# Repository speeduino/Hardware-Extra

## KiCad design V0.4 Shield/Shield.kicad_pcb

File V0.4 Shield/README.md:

<div align="center">

[]

##### A low cost, DIY friendly Engine Management System (ECU) based on the Arduino framework
</div>

## Speeduino
The Speeduino project is a flexible, fully featured Engine Management Systems (EMS aka ECU) based on the low cost and open source Arduino platform. It provides the hardware, firmware and software components that make up an engine management system, all provided under open licenses. With over 1000 installations, Speeduino has matured into a product that meets the needs of the hobbyist and enthusiast community without driving prices to the levels of traditional aftermarket ECUs.

## Overview
This board is a shield designed to add an automotive connector to the v0.4 series of Speeduino ECUs. It also includes a VR conditioner on board and allows for 12v Hall effect signals (Such as on some GM engines) to be used directly. 

The connector used is a Delphi Sicma 39 pin 

## License
These designs are release under the [TAPR Open Hardware License v1.0](https://files.tapr.org/OHL/TAPR_Open_Hardware_License_v1.0.txt). 

## Support
In addition the manual referenced above, Speeduino has a large and very vibrant community of people to help out with your setup or any questions you might add. 

* [Speeduino Forum](https://speeduino.com/forum) 
* [Discord](hhttps://discord.com/invite/taXeNM6xNb)
* [Facebook](https://www.facebook.com/groups/191918764521976/)

## Contributors

This project exists thanks to all the people who contribute, both in terms of code and testing provided. If you'd like to get involved, please have a read through [Contributing](contributing.md) and then jump on Discord to discuss things further

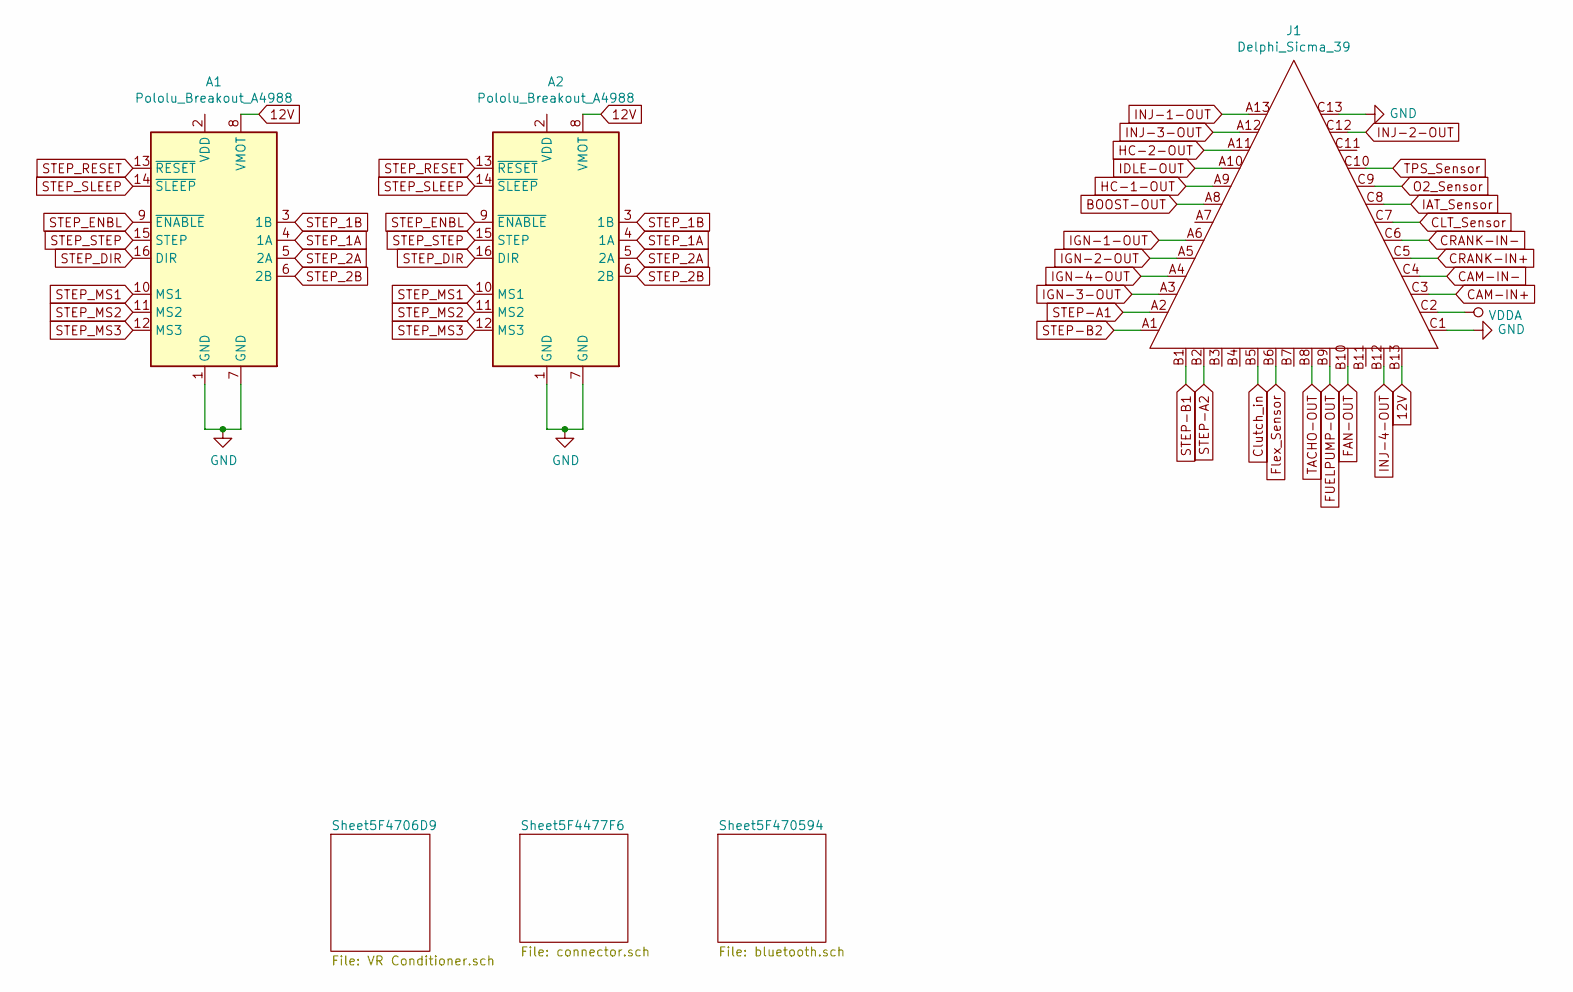
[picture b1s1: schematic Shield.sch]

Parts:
A1, A2: Pololu_Breakout_A4988; Pololu_Breakout-16_15.2x20.3mm; Manufacturer_Part_Number ESQ-108-14-L-S; Digikey Part Number SAM15571-ND
J1: Delphi_Sicma_39; Delphi_Sicma_39_Black

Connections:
12V: A1.8 (VMOT), A2.8 (VMOT), J1.B13
BOOST-OUT: J1.A8; also elsewhere on the board
CAM-IN+: J1.C3; also elsewhere on the board
CAM-IN-: J1.C4; also elsewhere on the board
CLT_Sensor: J1.C7; also elsewhere on the board
CRANK-IN+: J1.C5; also elsewhere on the board
CRANK-IN-: J1.C6; also elsewhere on the board
Clutch_in: J1.B5; also elsewhere on the board
FAN-OUT: J1.B10; also elsewhere on the board
FUELPUMP-OUT: J1.B9; also elsewhere on the board
Flex_Sensor: J1.B6; also elsewhere on the board
GND: A1.1 (GND), A1.7 (GND), A2.1 (GND), A2.7 (GND), J1.C1, J1.C13; also elsewhere on the board
HC-1-OUT: J1.A9; also elsewhere on the board
HC-2-OUT: J1.A11; also elsewhere on the board
IAT_Sensor: J1.C8; also elsewhere on the board
IDLE-OUT: J1.A10; also elsewhere on the board
IGN-1-OUT: J1.A6; also elsewhere on the board
IGN-2-OUT: J1.A5; also elsewhere on the board
IGN-3-OUT: J1.A3; also elsewhere on the board
IGN-4-OUT: J1.A4; also elsewhere on the board
INJ-1-OUT: J1.A13; also elsewhere on the board
INJ-2-OUT: J1.C12; also elsewhere on the board
INJ-3-OUT: J1.A12; also elsewhere on the board
INJ-4-OUT: J1.B12; also elsewhere on the board
O2_Sensor: J1.C9; also elsewhere on the board
STEP-A1: J1.A2; also elsewhere on the board
STEP-A2: J1.B2; also elsewhere on the board
STEP-B1: J1.B1; also elsewhere on the board
STEP-B2: J1.A1; also elsewhere on the board
STEP_1A: A1.4 (1A), A2.4 (1A)
STEP_1B: A1.3 (1B), A2.3 (1B)
STEP_2A: A1.5 (2A), A2.5 (2A)
STEP_2B: A1.6 (2B), A2.6 (2B)
STEP_DIR: A1.16 (DIR), A2.16 (DIR)
STEP_ENBL: A1.9 (~ENABLE), A2.9 (~ENABLE)
STEP_MS1: A1.10 (MS1), A2.10 (MS1)
STEP_MS2: A1.11 (MS2), A2.11 (MS2)
STEP_MS3: A1.12 (MS3), A2.12 (MS3)
STEP_RESET: A1.13 (~RESET), A2.13 (~RESET)
STEP_SLEEP: A1.14 (~SLEEP), A2.14 (~SLEEP)
STEP_STEP: A1.15 (STEP), A2.15 (STEP)
TACHO-OUT: J1.B8; also elsewhere on the board
TPS_Sensor: J1.C10; also elsewhere on the board
VDDA: J1.C2; also elsewhere on the board

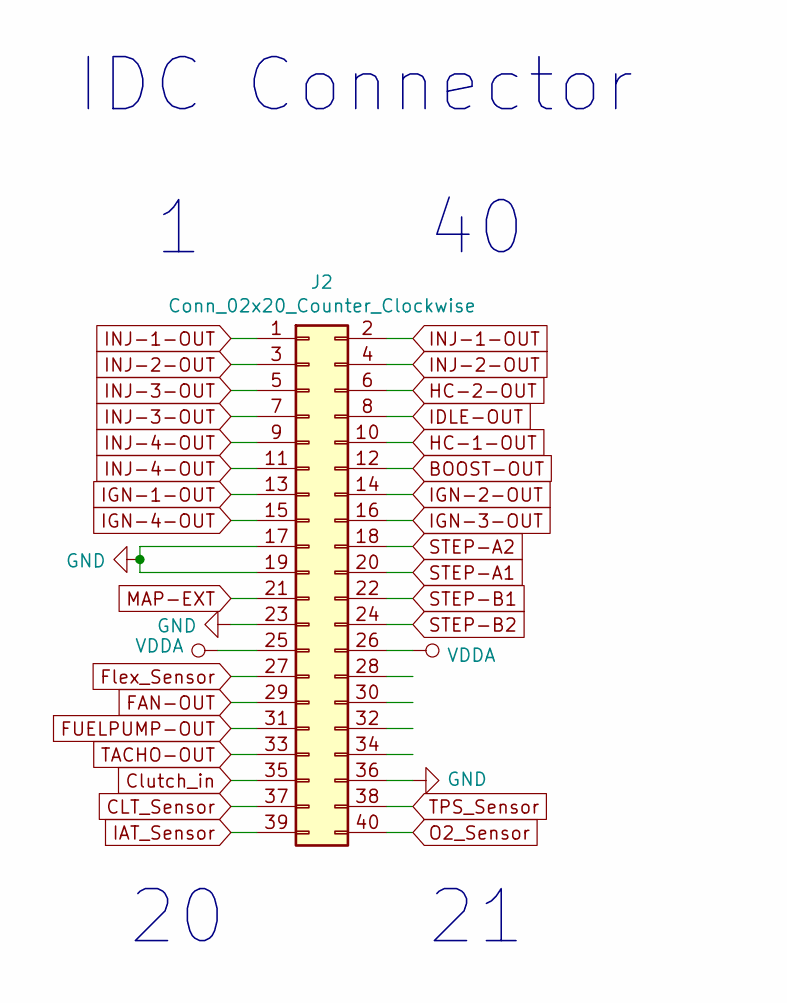
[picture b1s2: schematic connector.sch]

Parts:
J2: Conn_02x20_Counter_Clockwise; IDC-Header_2x20_P2.54mm_Vertical; Manufacturer_Part_Number SFH11-PBPC-D20-ST-BK; Digikey Part Number S9200-ND

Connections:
BOOST-OUT: J2.12; also elsewhere on the board
CLT_Sensor: J2.37; also elsewhere on the board
Clutch_in: J2.35; also elsewhere on the board
FAN-OUT: J2.29; also elsewhere on the board
FUELPUMP-OUT: J2.31; also elsewhere on the board
Flex_Sensor: J2.27; also elsewhere on the board
GND: J2.17, J2.19, J2.23, J2.36; also elsewhere on the board
HC-1-OUT: J2.10; also elsewhere on the board
HC-2-OUT: J2.6; also elsewhere on the board
IAT_Sensor: J2.39; also elsewhere on the board
IDLE-OUT: J2.8; also elsewhere on the board
IGN-1-OUT: J2.13; also elsewhere on the board
IGN-2-OUT: J2.14; also elsewhere on the board
IGN-3-OUT: J2.16; also elsewhere on the board
IGN-4-OUT: J2.15; also elsewhere on the board
INJ-1-OUT: J2.1, J2.2; also elsewhere on the board
INJ-2-OUT: J2.3, J2.4; also elsewhere on the board
INJ-3-OUT: J2.5, J2.7; also elsewhere on the board
INJ-4-OUT: J2.9, J2.11; also elsewhere on the board
MAP-EXT: J2.21
O2_Sensor: J2.40; also elsewhere on the board
STEP-A1: J2.20; also elsewhere on the board
STEP-A2: J2.18; also elsewhere on the board
STEP-B1: J2.22; also elsewhere on the board
STEP-B2: J2.24; also elsewhere on the board
TACHO-OUT: J2.33; also elsewhere on the board
TPS_Sensor: J2.38; also elsewhere on the board
VDDA: J2.25, J2.26; also elsewhere on the board

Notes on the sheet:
IDC Connector

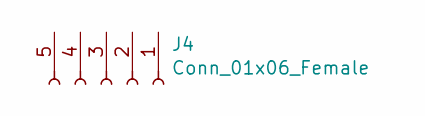
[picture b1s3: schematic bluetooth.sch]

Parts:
J4: Conn_01x06_Female; PinHeader_1x06_P2.54mm_Vertical

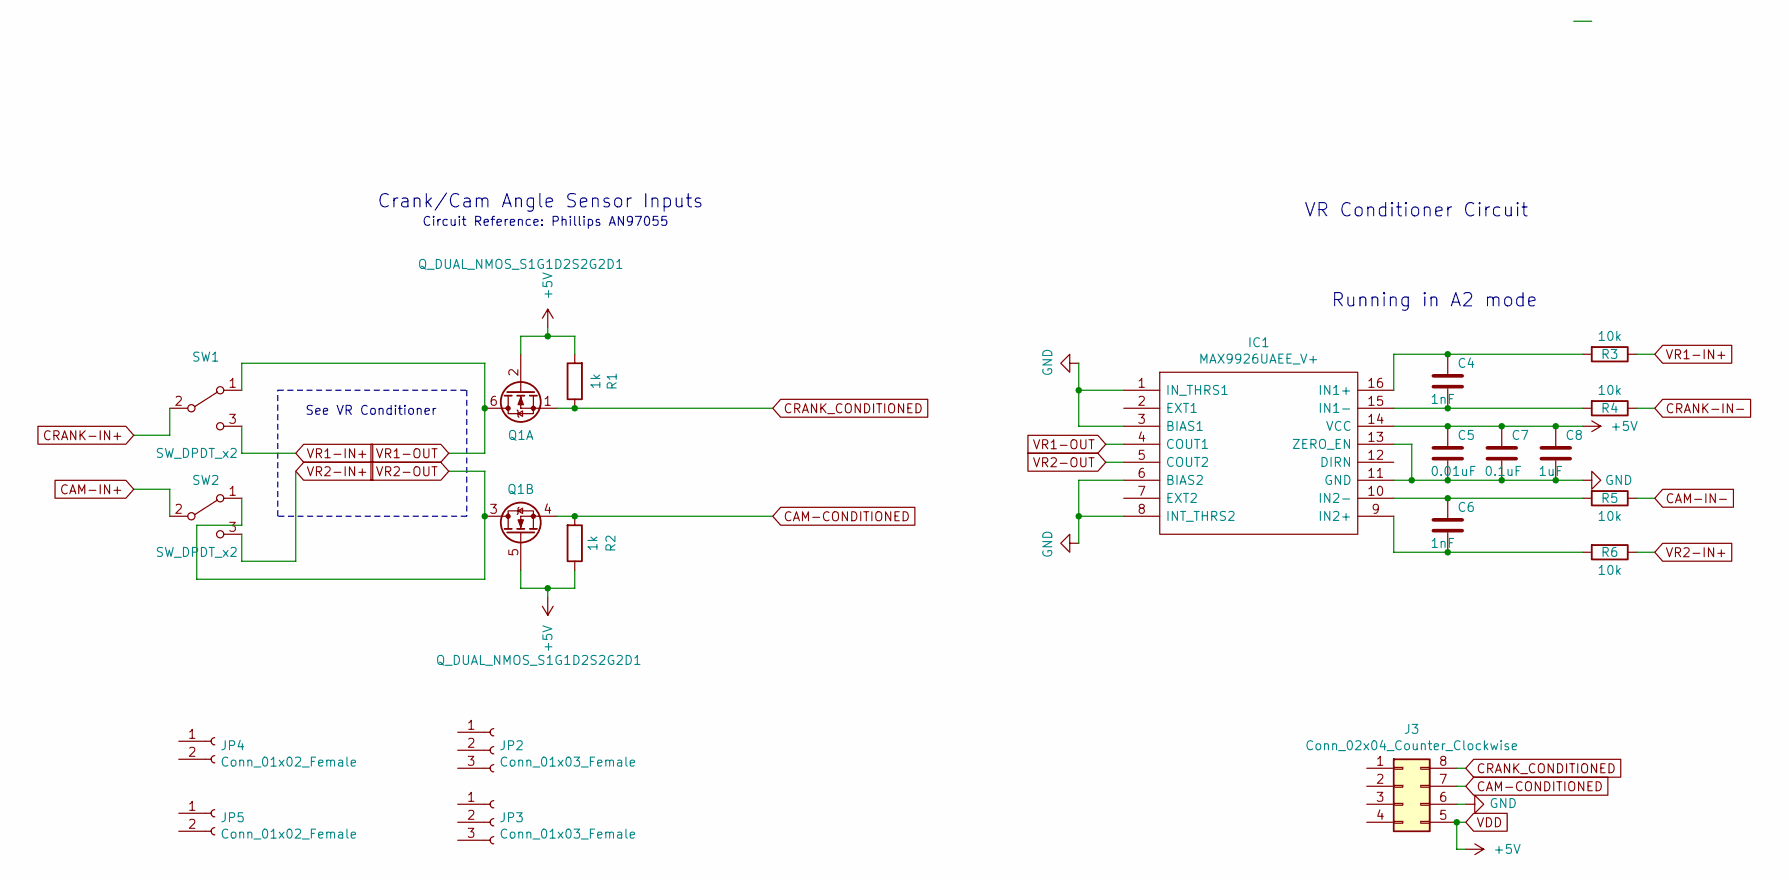
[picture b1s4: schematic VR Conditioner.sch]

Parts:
C4, C6: 1nF; C_0805_2012Metric; Manufacturer_Part_Number C0805C102J5HACAUTO; Digikey Part Number 399-16591-1-ND
C5: 0.01uF; C_0805_2012Metric; Manufacturer_Part_Number CC0805KRX7R9BB103; Digikey Part Number 311-1136-1-ND
C7: 0.1uF; C_0805_2012Metric; Manufacturer_Part_Number C0805C104M5RACAUTO; Digikey Part Number 399-12977-1-ND
C8: 1uF; C_0805_2012Metric; Manufacturer_Part_Number C0805C105K4RACAUTO; Digikey Part Number 399-6930-1-ND
IC1: MAX9926UAEE_V+; QSOP-16_3.9x4.9mm_P0.635mm; Manufacturer_Part_Number MAX9926UAEE/V+; Mouser Part Number 700-MAX9926UAEE/V+
J3: Conn_02x04_Counter_Clockwise; DIP-8_W7.62mm
JP2, JP3: Conn_01x03_Female; PinHeader_1x03_P2.54mm_Vertical
JP4, JP5: Conn_01x02_Female; PinHeader_1x02_P2.54mm_Vertical
Q1: Q_DUAL_NMOS_S1G1D2S2G2D1; SOT-363_SC-70-6; Manufacturer_Part_Number NTJD5121NT1G; Digikey Part Number NTJD5121NT1GOSCT-ND
R1, R2: 1k; R_0805_2012Metric; Manufacturer_Part_Number RC0805FR-071KL; Digikey Part Number 311-1.00KCRCT-ND
R3, R4, R5, R6: 10k; R_0805_2012Metric; Manufacturer_Part_Number RC0805JR-0710KL; Digikey Part Number 311-10KARCT-ND
SW1, SW2: SW_DPDT_x2; AYZ0202AGRLC; Manufacturer_Part_Number AYZ0202AGRLC; Digikey Part Number 401-2013-1-ND

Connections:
CAM-CONDITIONED: J3.7, Q1.4 (S), R2.2
CAM-IN+: SW2.2 (B); also elsewhere on the board
CAM-IN-: R5.1; also elsewhere on the board
CRANK-IN+: SW1.2 (B); also elsewhere on the board
CRANK-IN-: R4.1; also elsewhere on the board
CRANK_CONDITIONED: J3.8, Q1.1 (S), R1.1
GND: C5.2, C7.2, C8.2, IC1.1 (IN_THRS1), IC1.3 (BIAS1), IC1.6 (BIAS2), IC1.8 (INT_THRS2), IC1.11 (GND), IC1.13 (ZERO_EN), J3.6; also elsewhere on the board
unnamed: C4.1, IC1.16 (IN1+), R3.2
unnamed: C4.2, IC1.15 (IN1-), R4.2
unnamed: C6.1, IC1.10 (IN2-), R5.2
unnamed: C6.2, IC1.9 (IN2+), R6.2
VDD: C5.1, C7.1, C8.1, IC1.14 (VCC), J3.5, Q1.2 (G), Q1.5 (G), R1.2, R2.1
VR1-IN+: R3.1, SW1.3 (C)
VR1-OUT: IC1.4 (COUT1), Q1.6 (D), SW1.1 (A)
VR2-IN+: R6.1, SW2.3 (C)
VR2-OUT: IC1.5 (COUT2), Q1.3 (D), SW2.1 (A)

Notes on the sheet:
Crank/Cam Angle Sensor Inputs
VR Conditioner Circuit
Running in A2 mode
See VR Conditioner
Circuit Reference: Phillips AN97055

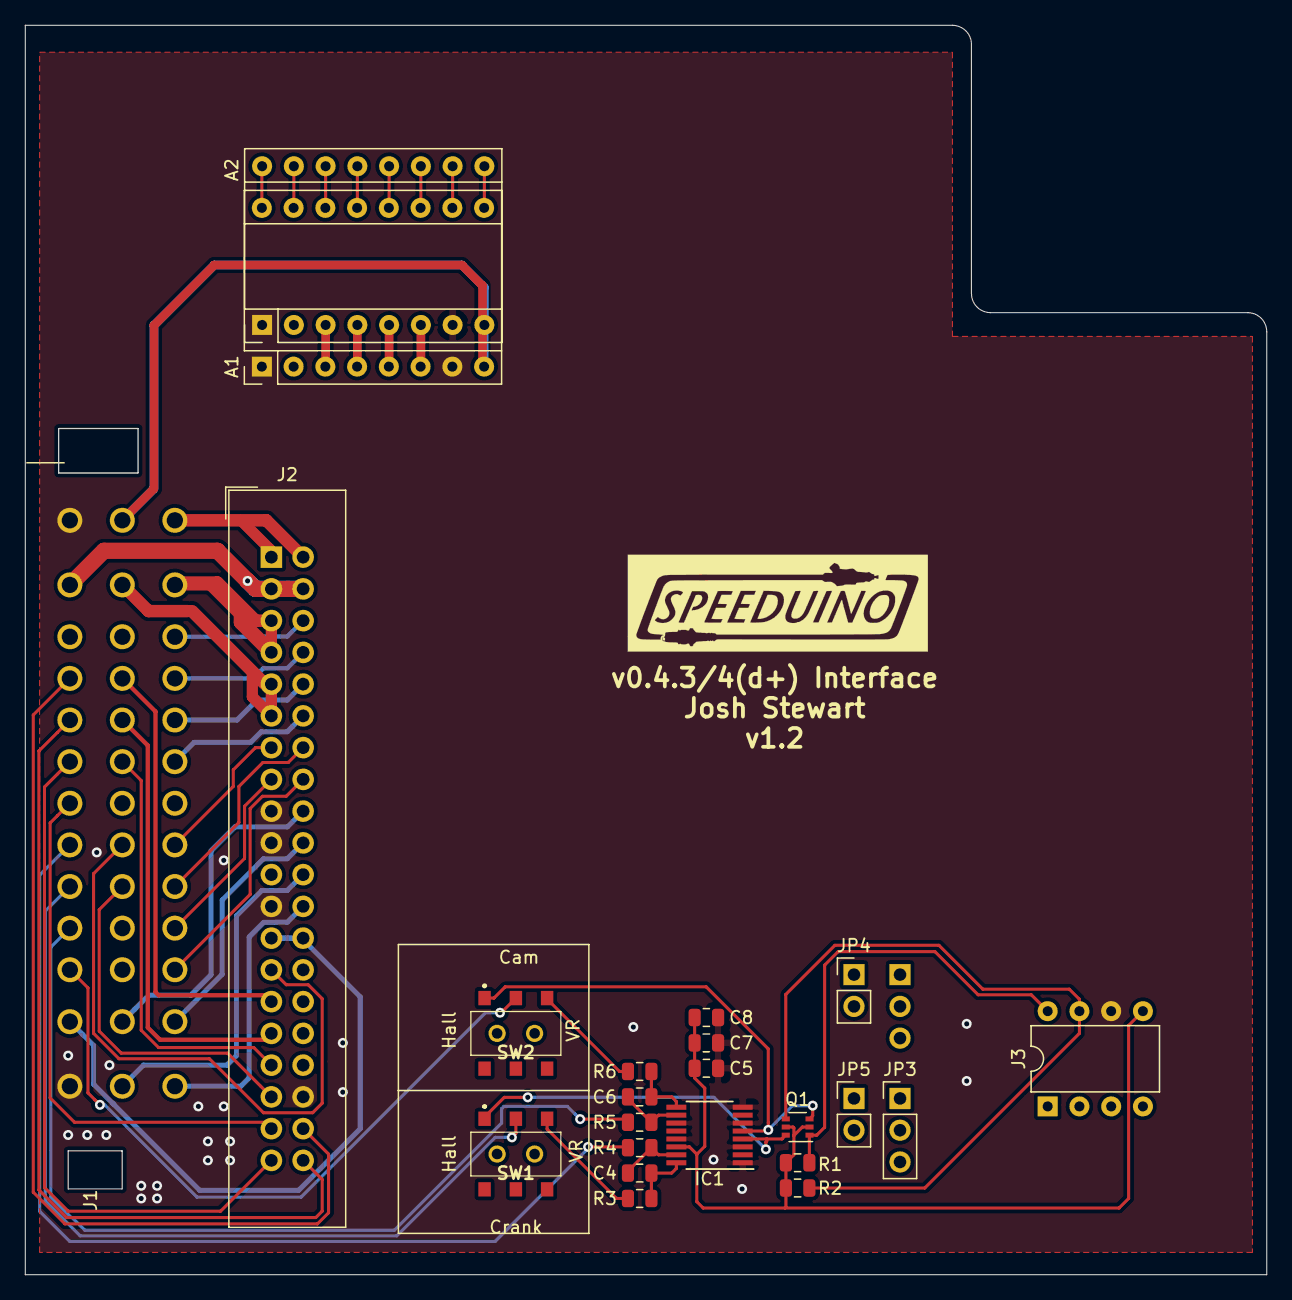
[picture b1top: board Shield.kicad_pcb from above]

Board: 2 copper layers, 99.3 x 99.9 mm, 24 parts (1 on the bottom side), 55 nets.

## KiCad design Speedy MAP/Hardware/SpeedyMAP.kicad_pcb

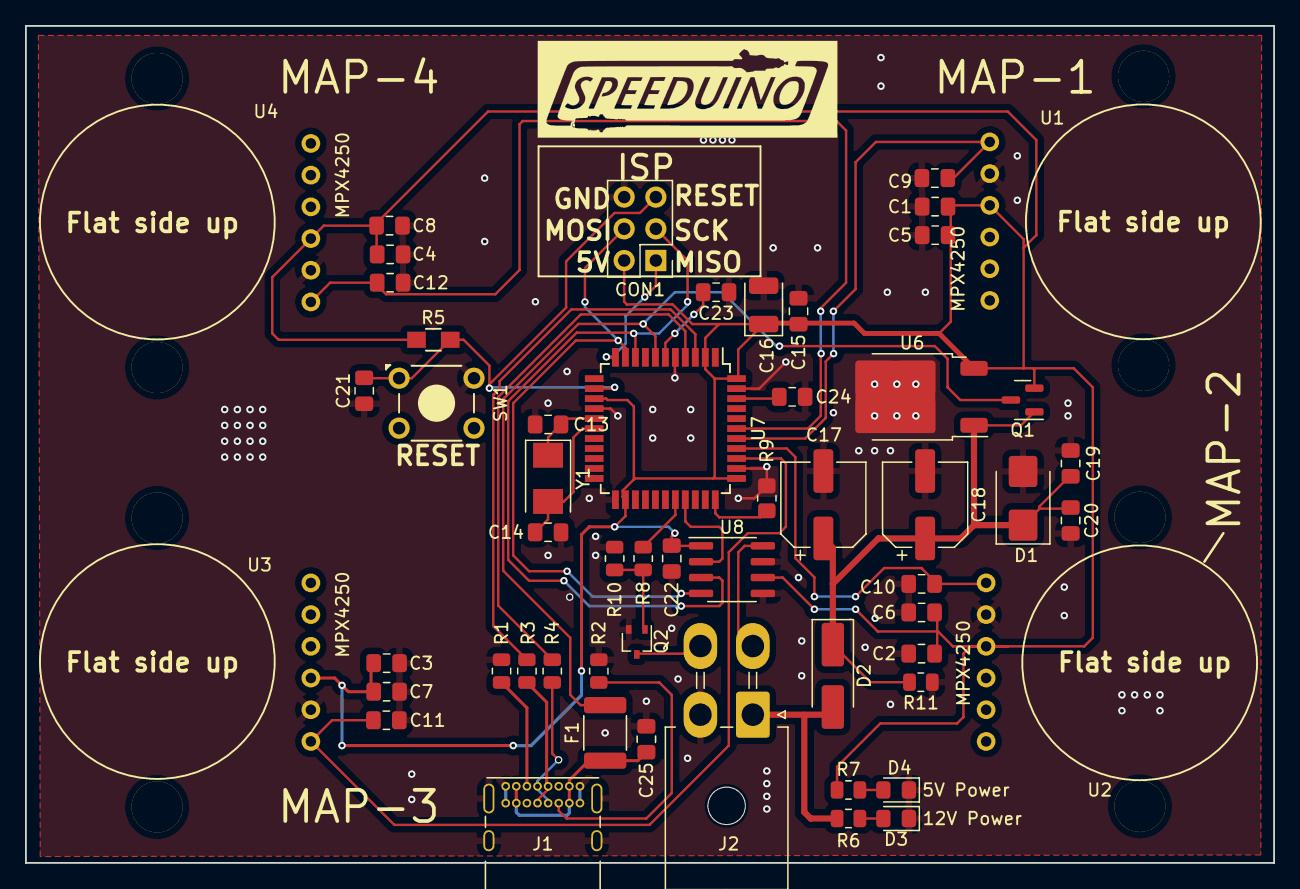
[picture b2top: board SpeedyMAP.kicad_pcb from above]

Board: 2 copper layers, 100.0 x 67.1 mm, 55 parts (0 on the bottom side), 32 nets.

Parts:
C1, C2, C3, C4, C23, C25: 1uF; C_0805_2012Metric_Pad1.18x1.45mm_HandSolder
C5, C6, C7, C8: 0.01uF; C_0805_2012Metric_Pad1.18x1.45mm_HandSolder
C9, C10, C11, C12: 0.3uF; C_0805_2012Metric_Pad1.18x1.45mm_HandSolder
C13, C14: 22pF; C_0805_2012Metric_Pad1.18x1.45mm_HandSolder
C15, C19, C22, C24: 0.1uF; C_0805_2012Metric_Pad1.18x1.45mm_HandSolder
C16: 47uF; CP_EIA-3528-21_Kemet-B
C17, C18: 33uF; CP_Elec_6.3x7.7
C20: 0.33uF; C_0805_2012Metric_Pad1.18x1.45mm_HandSolder
C21: 4.7nF; C_0805_2012Metric_Pad1.18x1.45mm_HandSolder
CON1: AVR-ISP-6; PinHeader_2x03_P2.54mm_Vertical
D1: D_TVS; D_SMB
D2: D_Schottky; D_SMA_Handsoldering
D3, D4: LED; LED_0805_2012Metric_Pad1.15x1.40mm_HandSolder
F1: Fuse; Fuse_1812_4532Metric_Pad1.30x3.40mm_HandSolder
J1: USB_C_Receptacle; USB_C_Receptacle_GCT_USB4085
J2: Conn_01x04; Molex_Mini-Fit_Jr_5569-04A2_2x02_P4.20mm_Horizontal
Q1: FDN340P; SOT-23
Q2: BSS138PW,115; SOT-323_SC-70
R1, R2: 5.1k; R_0805_2012Metric
R3, R4: 22; R_0805_2012Metric
R5: R10k; R_0805_HandSoldering
R6, R8: 1k; R_0805_2012Metric
R7: 470R; R_0805_2012Metric
R9: R10k; R_0805_2012Metric_Pad1.20x1.40mm_HandSolder
R10, R11: 100k; R_0805_2012Metric
SW1: SW_SPST; SW_TH_Tactile_Omron_B3F-10xx
U1, U2, U3, U4: MPX4250
U6: MC78M05_TO252; TO-252-2
U7: ATmega32U4-A; TQFP-44_10x10mm_P0.8mm
U8: MCP4921-E/SN; SOIC-8_3.9x4.9mm_P1.27mm
Y1: Crystal; Crystal_SMD_5032-2Pin_5.0x3.2mm

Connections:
12V-PROT: C17.1, C18.1, C19.1, C20.1, D1.1 (K), D2.1 (K), Q1.1 (G), R11.2, U6.1 (VI)
12V-SW: D2.2 (A), J2.1, R6.1
+5V: C1.1, C2.1, C3.1, C4.1, C5.1, C6.1, C7.1, C8.1, C15.1, C16.1, C22.2, CON1.2, Q1.2 (S), R5.1, R7.1, U1.3 (VCC), U2.3 (VCC), U3.3 (VCC), U4.3 (VCC), U6.3 (VO), U7.2 (UVCC), U7.14 (VCC), U7.24 (AVCC), U7.34 (VCC), U7.44 (AVCC), U8.1 (VDD), U8.6 (VrefA)
D+: R4.2, U7.4 (D+)
D-: R3.1, U7.3 (D-)
DAC_SS: U7.30 (PB6), U8.2 (~CS)
GND: C1.2, C2.2, C3.2, C4.2, C5.2, C6.2, C7.2, C8.2, C9.2, C10.2, C11.2, C12.2, C13.1, C14.1, C15.2, C16.2, C17.2, C18.2, C19.2, C20.2, C21.1, C22.1, C23.1, C24.1, C25.2, CON1.6, D1.2 (A), D3.1 (K), D4.1 (K), J1.A1 (GND), J1.A12 (GND), J1.B1 (GND), J1.B12 (GND), J1.S1 (SHIELD), J2.2, Q2.2 (S), R1.2, R2.1, R9.1, R10.1, R11.1, SW1.2 (B), U1.2 (GND), U2.2 (GND), U3.2 (GND), U4.2 (GND), U6.2 (GND), U7.5 (UGND), U7.15 (GND), U7.23 (GND), U7.35 (GND), U7.43 (GND), U8.5 (~LDAC), U8.7 (AVSS)
MAP1: C9.1, U1.1 (VOUT), U7.38 (PF5)
MAP2: C10.1, U2.1 (VOUT), U7.37 (PF6)
MAP3: C11.1, U3.1 (VOUT), U7.36 (PF7)
MAP4: C12.1, U4.1 (VOUT), U7.39 (PF4)
MAP_Out: J2.3, U8.8 (VoutA)
MCU-D9: R8.1, U7.29 (PB5)
MISO: CON1.1, U7.11 (PB3)
MOSI: CON1.4, U7.10 (PB2), U8.4 (SDI)
unnamed: C25.1, F1.1, J1.A4 (VBUS), J1.A9 (VBUS), J1.B4 (VBUS), J1.B9 (VBUS)
unnamed: D3.2 (A), R6.2
unnamed: D4.2 (A), R7.2
unnamed: J1.A5 (CC1), R1.1
unnamed: J1.B5 (CC2), R2.2
unnamed: J1.A6 (D+), J1.B6 (D+), R4.1
unnamed: J1.A7 (D-), J1.B7 (D-), R3.2
unnamed: Q2.1 (G), R8.2, R10.2
unnamed: C24.2, U7.42 (AREF)
unnamed: C23.2, U7.6 (UCAP)
unnamed: C14.2, U7.17 (XTAL1), Y1.2
unnamed: C13.2, U7.16 (XTAL2), Y1.1
unnamed: R9.2, U7.33 (~HWB/PE2)
RESET: C21.2, CON1.5, R5.2, SW1.1 (A), U7.13 (~RESET)
SCK: CON1.3, U7.9 (PB1), U8.3 (SCK)
Tach_Out: J2.4, Q2.3 (D)
VBUS: F1.2, Q1.3 (D), U7.7 (VBUS)

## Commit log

2024-06-16 Initial hardware dump
